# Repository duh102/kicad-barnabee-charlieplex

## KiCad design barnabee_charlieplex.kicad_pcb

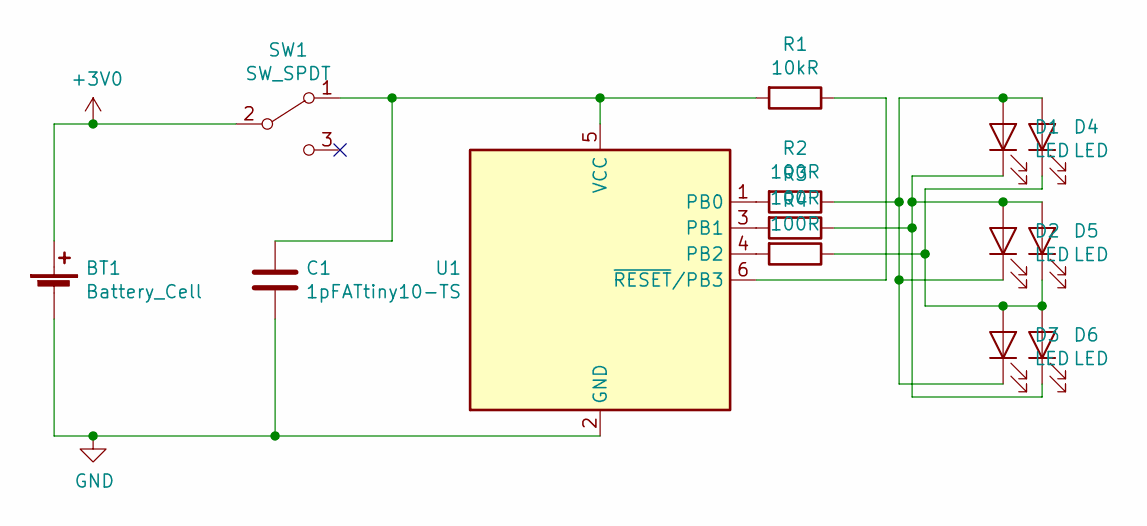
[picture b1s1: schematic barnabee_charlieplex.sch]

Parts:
BT1: Battery_Cell; BatteryHolder_Keystone_3034_1x20mm
C1: 1pF; C_0805_2012Metric
D1, D2, D3, D4, D5, D6: LED; LED_0805_2012Metric
R1: 10kR; R_0805_2012Metric
R2, R3, R4: 100R; R_0805_2012Metric
SW1: SW_SPDT; CJS-1200TB
U1: ATtiny10-TS; SOT-23-6

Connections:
+3V0: BT1.1 (+), SW1.2 (B)
GND: BT1.2 (-), C1.2, U1.2 (GND)
unnamed: C1.1, R1.2, SW1.1 (A), U1.5 (VCC)
unnamed: D1.1 (K), D2.2 (A), D5.2 (A), D6.1 (K), R3.1
unnamed: D1.2 (A), D2.1 (K), D3.1 (K), D4.2 (A), R2.1
unnamed: D3.2 (A), D4.1 (K), D5.1 (K), D6.2 (A), R4.1
unnamed: R1.1, U1.6 (~RESET~/PB3)
unnamed: R2.2, U1.1 (PB0)
unnamed: R3.2, U1.3 (PB1)
unnamed: R4.2, U1.4 (PB2)

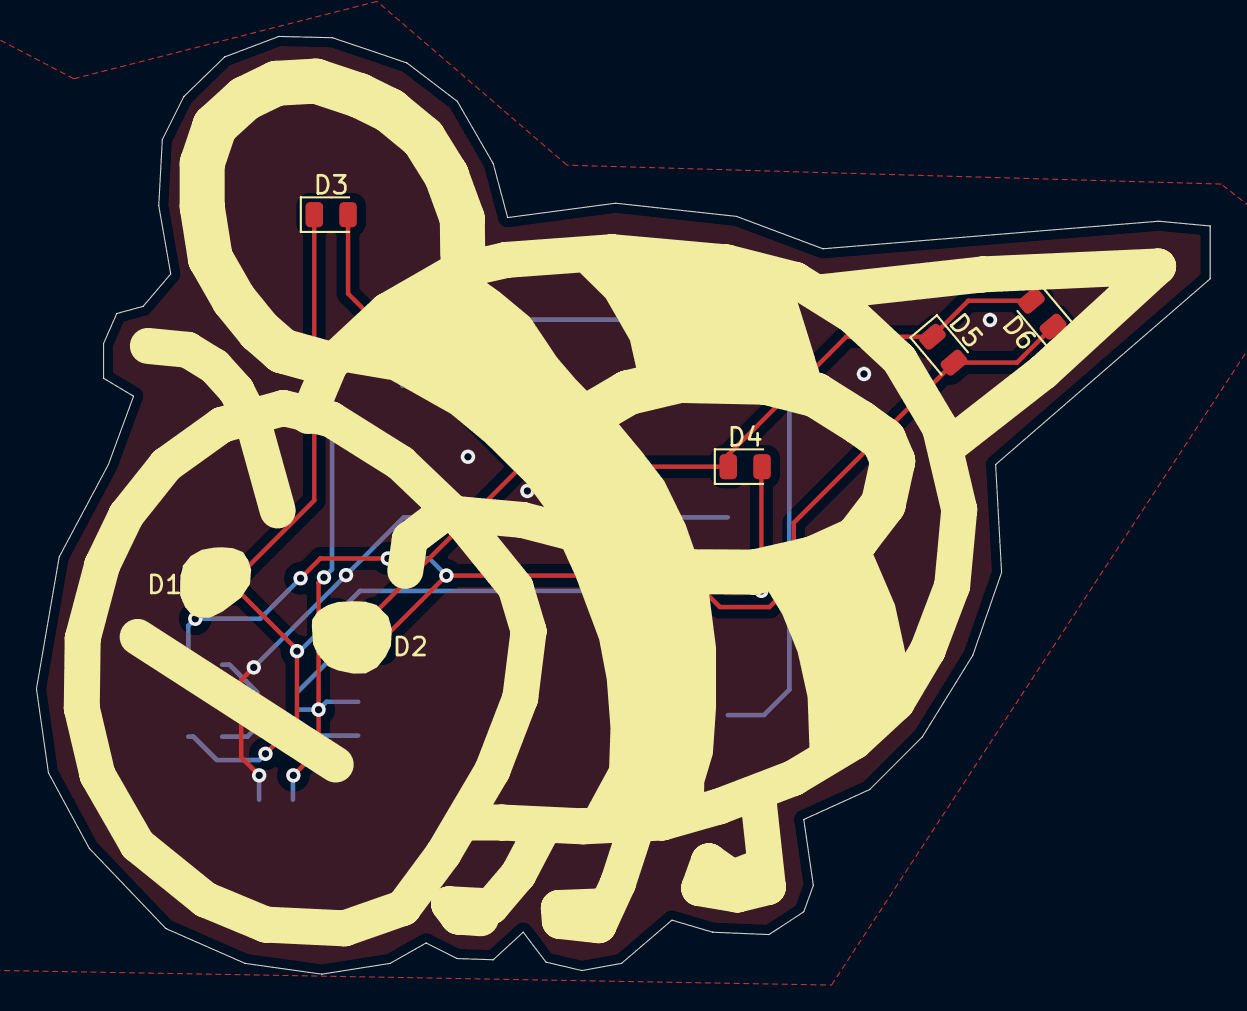
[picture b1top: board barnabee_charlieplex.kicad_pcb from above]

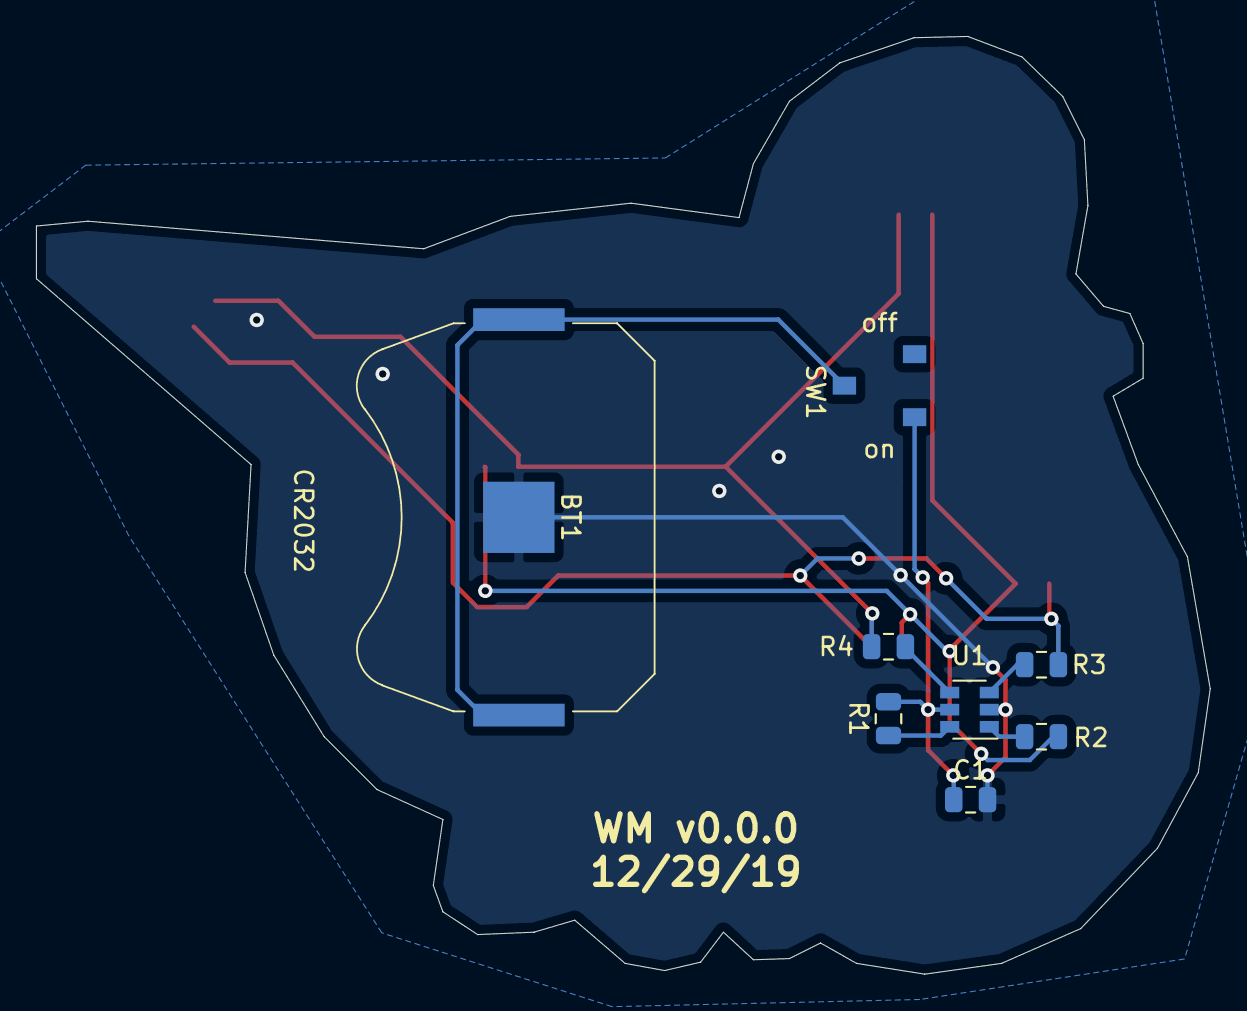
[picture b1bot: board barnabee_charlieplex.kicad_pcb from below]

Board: 2 copper layers, 65.2 x 52.1 mm, 14 parts (8 on the bottom side), 10 nets.

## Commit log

2020-12-09 Some minor updates
